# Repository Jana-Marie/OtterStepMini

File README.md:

# OtterStepMini

OtterStepMini is a user friendly, up to 48V 10A stepper-motor-driver. It can be controlled via RS485 or USB-CDC and also comes with a 100W USB-PD input, for extra convinience on stepper-motor testing and for small desktop applications (e.g. 3D-scanner turntable).

**The board has not been tested and should not be ordered yet.**

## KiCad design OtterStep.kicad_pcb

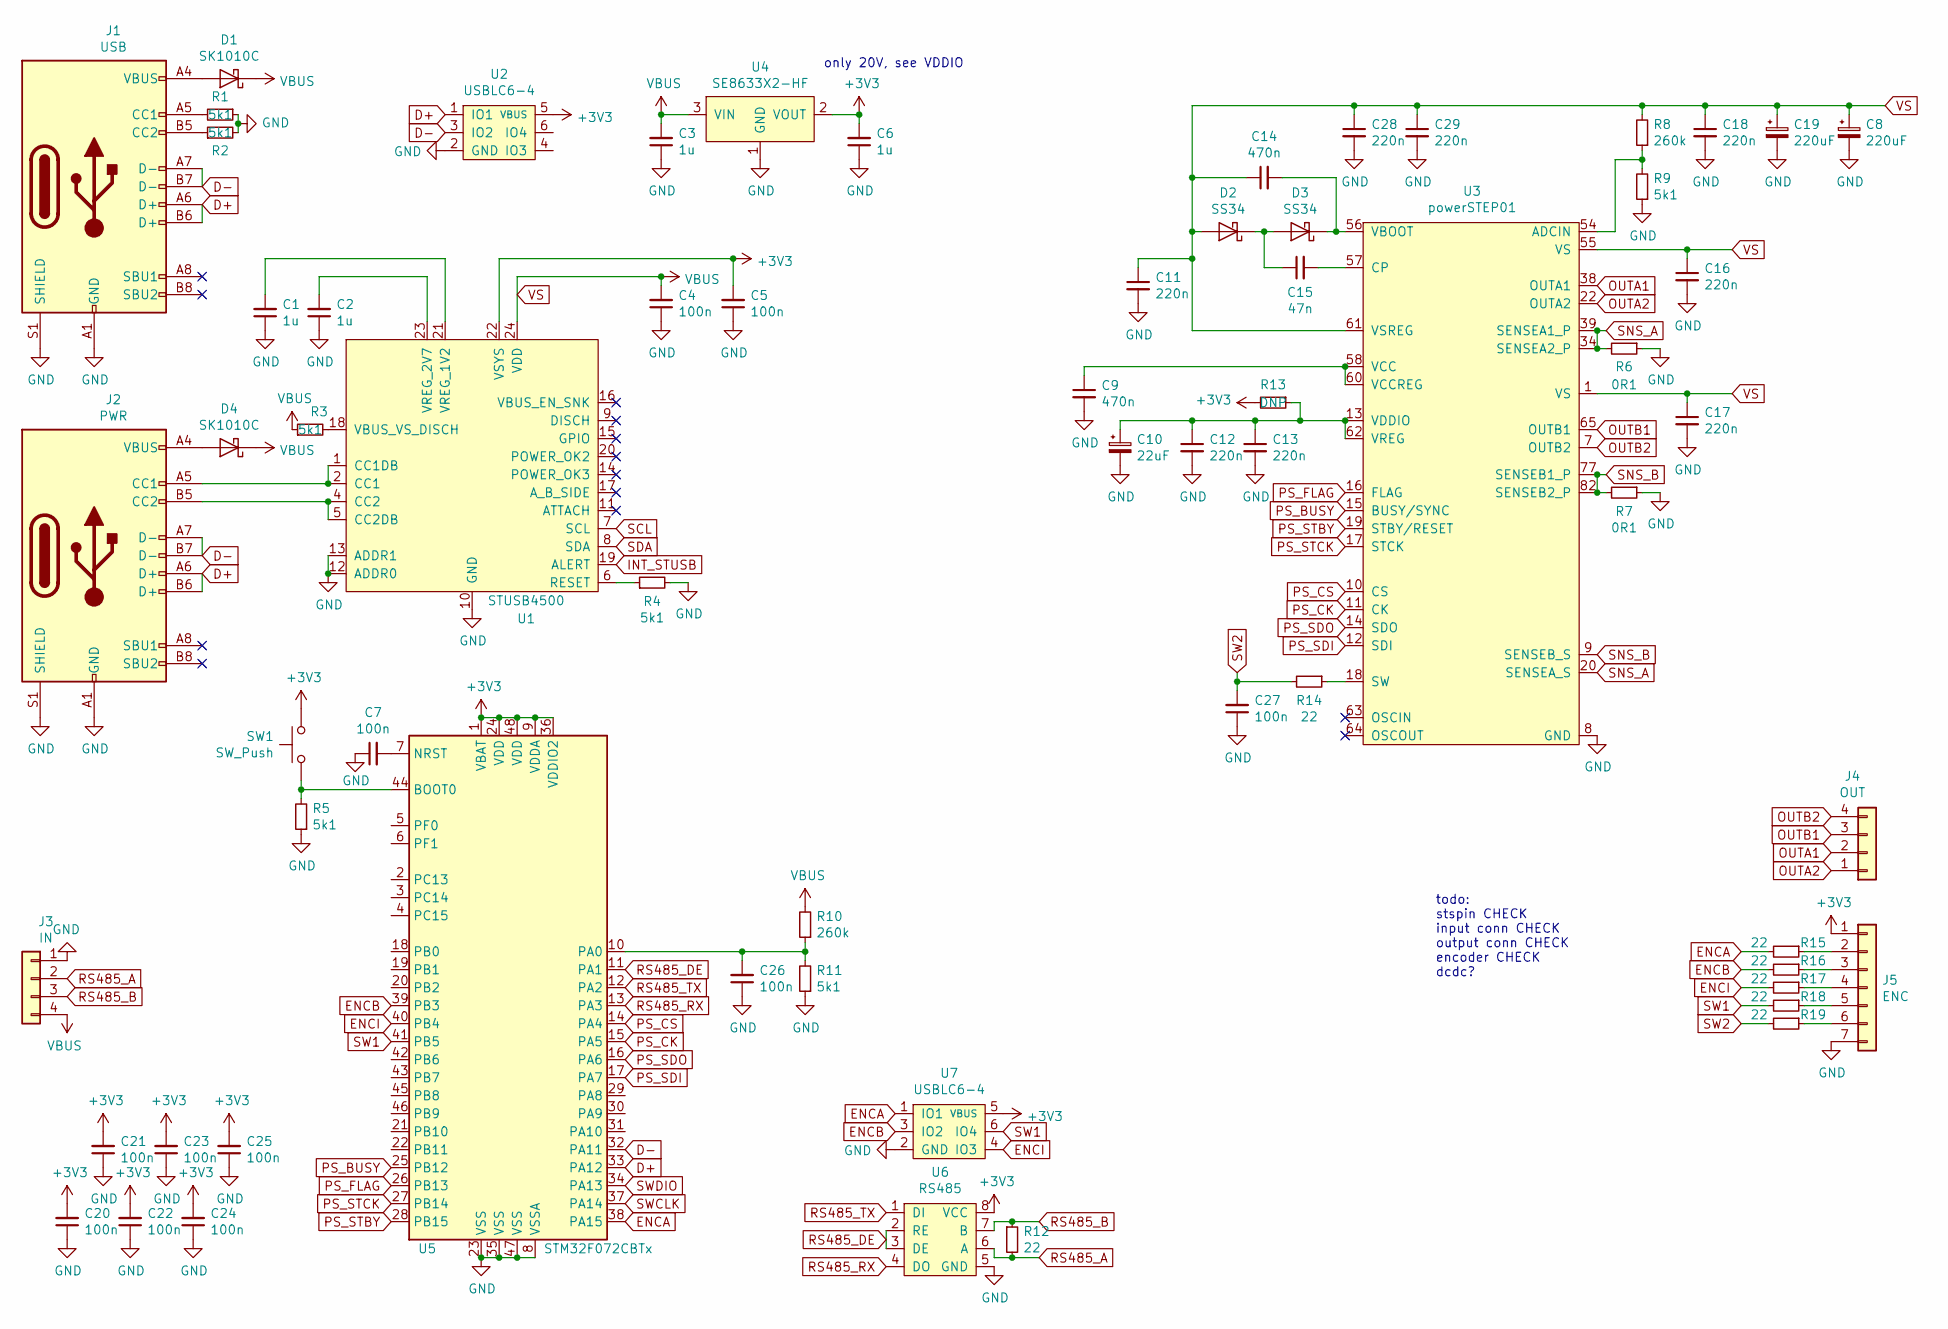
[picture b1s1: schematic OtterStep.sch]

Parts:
C1, C2, C3, C6: 1u; C_0402
C4, C5, C7, C20, C21, C22, C23, C24, C25, C26, C27: 100n; C_0402
C8, C19: 220uF; CP_Elec_18x17.5
C9, C14: 470n; C_0805
C10: 22uF; CP_Elec_10x10
C11, C12, C13, C16, C17, C18, C28, C29: 220n; C_0805
C15: 47n; C_0805
D1, D4: SK1010C; D_SMC
D2, D3: SS34; D_SOD-123
J1: USB; USB-C 16Pin
J2: PWR; USB-C 16Pin
J3: IN; PhoenixContact_MSTBA_2,5_4-G_1x04_P5.00mm_Horizontal
J4: OUT; PhoenixContact_MSTBA_2,5_4-G_1x04_P5.00mm_Horizontal
J5: ENC; PhoenixContact_MC_1,5_7-G-3.5_1x07_P3.50mm_Horizontal
R1, R2, R3, R4, R5, R9, R11: 5k1; R_0402
R6, R7: 0R1; R_1206_3216Metric
R8, R10: 260k; R_0402
R12, R14, R15, R16, R17, R18, R19: 22; R_0402
R13: DNP; R_0402
SW1: SW_Push; SW_SPST_EVQP7C
U1: STUSB4500; QFN-24-1EP_4x4mm_P0.5mm_EP2.7x2.7mm
U2, U7: USBLC6-4; SOT-23-6
U3: powerSTEP01
U4: SE8633X2-HF; SOT-23
U5: STM32F072CBTx; LQFP-48_7x7mm_P0.5mm
U6: RS485; SO-8_3.9x4.9mm_P1.27mm

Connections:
+3V3: C5.2, C6.2, C20.2, C21.2, C22.2, C23.2, C24.2, C25.2, J5.1, R13.2, SW1.2, U1.22 (VSYS), U2.5 (VBUS), U4.2 (VOUT), U5.1 (VBAT), U5.9 (VDDA), U5.24 (VDD), U5.36 (VDDIO2), U5.48 (VDD), U6.8 (VCC), U7.5 (VBUS)
D+: J1.A6 (D+), J1.B6 (D+), J2.A6 (D+), J2.B6 (D+), U2.1 (IO1), U5.33 (PA12)
D-: J1.A7 (D-), J1.B7 (D-), J2.A7 (D-), J2.B7 (D-), U2.3 (IO2), U5.32 (PA11)
ENCA: R15.2, U5.38 (PA15), U7.1 (IO1)
ENCB: R16.2, U5.39 (PB3), U7.3 (IO2)
ENCI: R17.2, U5.40 (PB4), U7.4 (IO3)
GND: C1.1, C2.1, C3.1, C4.1, C5.1, C6.1, C7.1, C8.2, C9.2, C10.2, C11.2, C12.2, C13.2, C16.2, C17.2, C18.2, C19.2, C20.1, C21.1, C22.1, C23.1, C24.1, C25.1, C26.1, C27.1, C28.2, C29.2, J1.A1 (GND), J1.A12 (GND), J1.B1 (GND), J1.B12 (GND), J1.S1 (SHIELD), J2.A1 (GND), J2.A12 (GND), J2.B1 (GND), J2.B12 (GND), J2.S1 (SHIELD), J3.1, J5.7, R1.1, R2.2, R4.2, R5.1, R6.1, R7.1, R9.1, R11.1, U1.10 (GND), U1.12 (ADDR0), U1.13 (ADDR1), U1.25 (GND), U2.2 (GND), U3.8 (GND), U3.21 (GND), U3.59 (GND), U3.EPAD9 (GND), U4.1 (GND), U5.8 (VSSA), U5.23 (VSS), U5.35 (VSS), U5.47 (VSS), U6.5 (GND), U7.2 (GND)
INT_STUSB: U1.19 (ALERT)
unnamed: C1.2, U1.21 (VREG_1V2)
unnamed: C2.2, U1.23 (VREG_2V7)
unnamed: C7.2, U5.7 (NRST)
unnamed: C9.1, U3.58 (VCC), U3.60 (VCCREG)
unnamed: C10.1, C12.1, C13.1, R13.1, U3.13 (VDDIO), U3.62 (VREG)
unnamed: C14.2, D3.1 (K), U3.56 (VBOOT)
unnamed: C15.1, D2.1 (K), D3.2 (A)
unnamed: C15.2, U3.57 (CP)
unnamed: C26.2, R10.1, R11.2, U5.10 (PA0)
unnamed: D1.2 (A), J1.A4 (VBUS), J1.A9 (VBUS), J1.B4 (VBUS), J1.B9 (VBUS)
unnamed: D4.2 (A), J2.A4 (VBUS), J2.A9 (VBUS), J2.B4 (VBUS), J2.B9 (VBUS)
unnamed: J1.A5 (CC1), R1.2
unnamed: J1.B5 (CC2), R2.1
unnamed: J2.A5 (CC1), U1.1 (CC1DB), U1.2 (CC1)
unnamed: J2.B5 (CC2), U1.4 (CC2), U1.5 (CC2DB)
unnamed: J5.2, R15.1
unnamed: J5.3, R16.1
unnamed: J5.4, R17.1
unnamed: J5.5, R18.1
unnamed: J5.6, R19.1
unnamed: R3.2, U1.18 (VBUS_VS_DISCH)
unnamed: R4.1, U1.6 (RESET)
unnamed: R5.2, SW1.1, U5.44 (BOOT0)
unnamed: R8.1, R9.2, U3.54 (ADCIN)
unnamed: R14.1, U3.18 (SW)
OUTA1: J4.2, U3.38 (OUTA1), U3.42 (OUTA1), U3.53 (OUTA1), U3.EPAD4 (OUTA1)
OUTA2: J4.1, U3.22 (OUTA2), U3.33 (OUTA2), U3.37 (OUTA2), U3.EPAD3 (OUTA2)
OUTB1: J4.3, U3.65 (OUTB1), U3.76 (OUTB1), U3.80 (OUTB1), U3.EPAD7 (OUTB1)
OUTB2: J4.4, U3.7 (OUTB2), U3.81 (OUTB2), U3.85 (OUTB2), U3.EPAD8 (OUTB2)
PS_BUSY: U3.15 (BUSY/SYNC), U5.25 (PB12)
PS_CK: U3.11 (CK), U5.15 (PA5)
PS_CS: U3.10 (CS), U5.14 (PA4)
PS_FLAG: U3.16 (FLAG), U5.26 (PB13)
PS_SDI: U3.12 (SDI), U5.17 (PA7)
PS_SDO: U3.14 (SDO), U5.16 (PA6)
PS_STBY: U3.19 (STBY/RESET), U5.28 (PB15)
PS_STCK: U3.17 (STCK), U5.27 (PB14)
RS485_A: J3.2, R12.2, U6.6 (A)
RS485_B: J3.3, R12.1, U6.7 (B)
RS485_DE: U5.11 (PA1), U6.2 (RE), U6.3 (DE)
RS485_RX: U5.13 (PA3), U6.4 (DO)
RS485_TX: U5.12 (PA2), U6.1 (DI)
SCL: U1.7 (SCL)
SDA: U1.8 (SDA)
SNS_A: R6.2, U3.20 (SENSEA_S), U3.34 (SENSEA2_P), U3.39 (SENSEA1_P)
SNS_B: R7.2, U3.9 (SENSEB_S), U3.77 (SENSEB1_P), U3.82 (SENSEB2_P)
SW1: R18.2, U5.41 (PB5), U7.6 (IO4)
SW2: C27.2, R14.2, R19.2
SWCLK: U5.37 (PA14)
SWDIO: U5.34 (PA13)
VS: C3.2, C4.2, C8.1, C11.1, C14.1, C16.1, C17.1, C18.1, C19.1, C28.1, C29.1, D1.1 (K), D2.2 (A), D4.1 (K), J3.4, R3.1, R8.2, R10.2, U1.24 (VDD), U3.1 (VS), U3.23 (VS), U3.43 (VS), U3.55 (VS), U3.61 (VSREG), U3.66 (VS), U4.3 (VIN)

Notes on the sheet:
todo: stspin CHECK input conn CHECK output conn CHECK encoder CHECK dcdc?
only 20V, see VDDIO

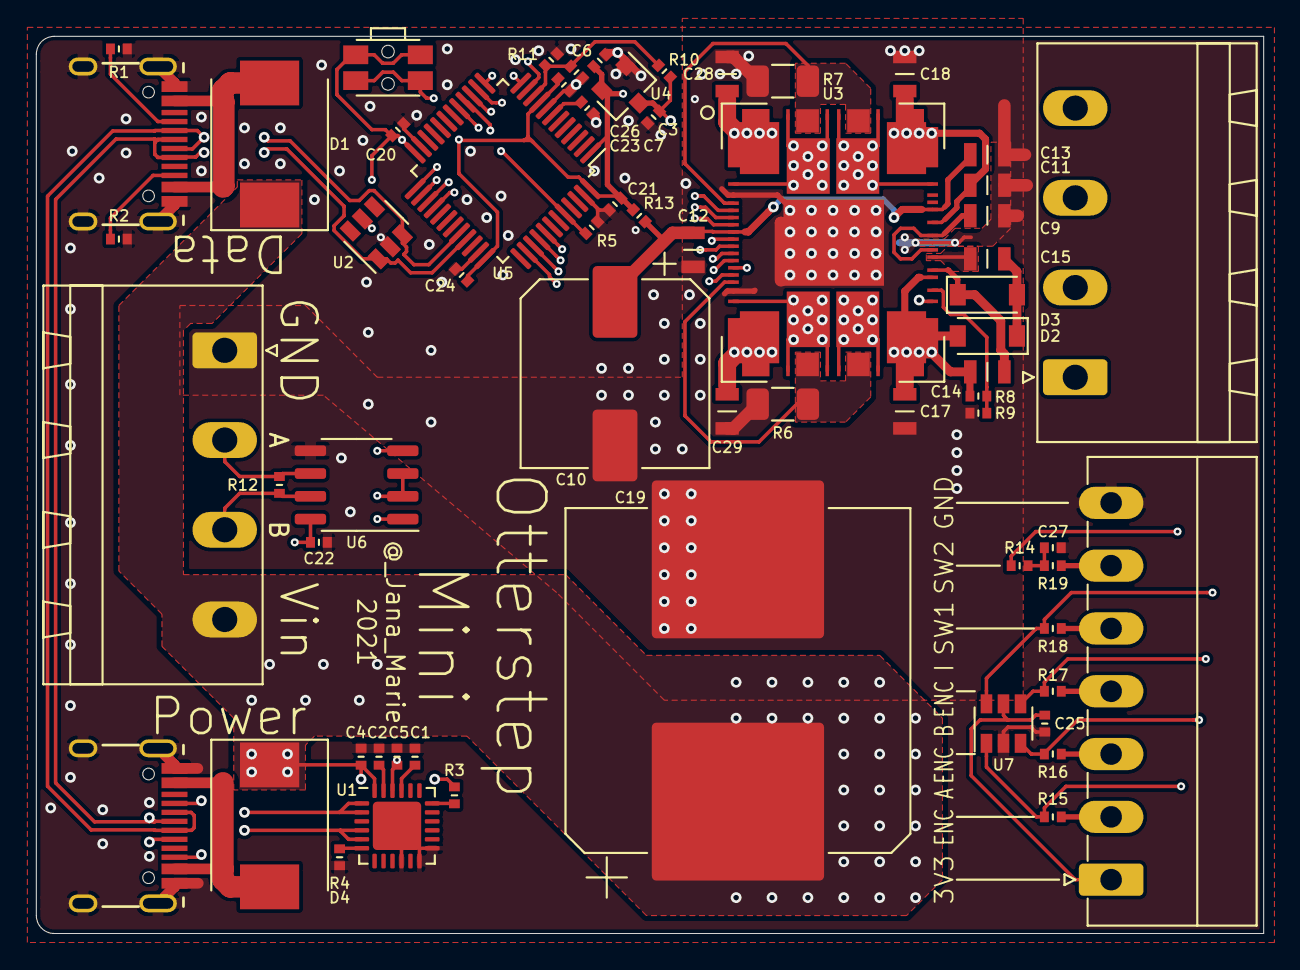
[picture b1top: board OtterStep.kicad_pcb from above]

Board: 4 copper layers, 68.4 x 50.0 mm, 63 parts (0 on the bottom side), 54 nets.

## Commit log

2021-07-17 updated files
2021-12-27 changed silk
2021-12-27 added images
